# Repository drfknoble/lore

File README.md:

# Low-Cost, Open-Source Robot for Education (LORE)

## Introduction

Welcome to my repository for my Low-Cost, Open-Source Robot for Education (LORE) project.

<div>

</div>

## Motivation

I started this project because I was approached by the House of Science, a Science, Technology, Engineering, and Mathematics (STEM) organisation in Tauranga, New Zealand, who needed a low-cost, i.e., less than NZD$100.00, platform that could be used to teach robotics.

The problem was: there wasn't anything on the market at met the organisation's needs, so I decided to build one for them.

## Aims

The aims of this project included:
- Developing a low-cost, mobile robot that can be used to teach beginner, intermediate, and advanced students how to program in C++.

## Objectives

The objectives of this project included:
- Creating accessible Computer Aided Design (CAD) files.
- Creating accessible Electronics Design Automation (EDA) files.
- Creating accessible source code and software libraries.
- Creating an easy-to-assemble mobile robot that uses an Arduino microcontroller, servo motors, and ultrasonic sensors.
- Writing clear-to-follow instructions of how to program the mobile robot.

## Repository Structure

The repository is organised as follows:

```console
/lore         
    /cad                          
        /solidworks                    
        /freecad  
        /fabrication
        /renders                     
    /pcb
        /eagle
        /kicad
        /fabrication
    /src
        /beginner
        /intermediate
        /advanced
        /ROBOT
    /doc                      
        /img
        /costing                
        /programming_guide
```

All CAD files can be found in the `/cad` sub-directory. I've included the original SOLIDWORKS files and the open-source equivalents.

All EDA files can be found in the `/pcb` sub-directory. I've included the original Eagle files and the open-source equivalents.

All source code and software libaries are included in the `/src` sub-directory. The `/ROBOT` sub-directory is the Arduino library that is used to program the robot.

Documentation is included in the `/doc` sub-directory.

## Tools Used

I used the following tools in this project:
- SOLIDWORKS and FreeCAD.
- Eagle and KiCAD.
- Microsoft Visual Studio and Arduino Integrated Development IDE (IDE).

Get FreeCAD here: https://www.freecadweb.org/.  
Get KiCAD here: https://www.kicad.org/.  
Get Arduino IDE here: https://www.arduino.cc/en/software.  
Get Visual Studio here: https://visualstudio.microsoft.com/.  

Alternatively, you can use Microsoft Visual Studio Code as the IDE.

Get Code here: https://code.visualstudio.com/.

## Credit

Dr Frazer K. Noble  
http://drfknoble.com

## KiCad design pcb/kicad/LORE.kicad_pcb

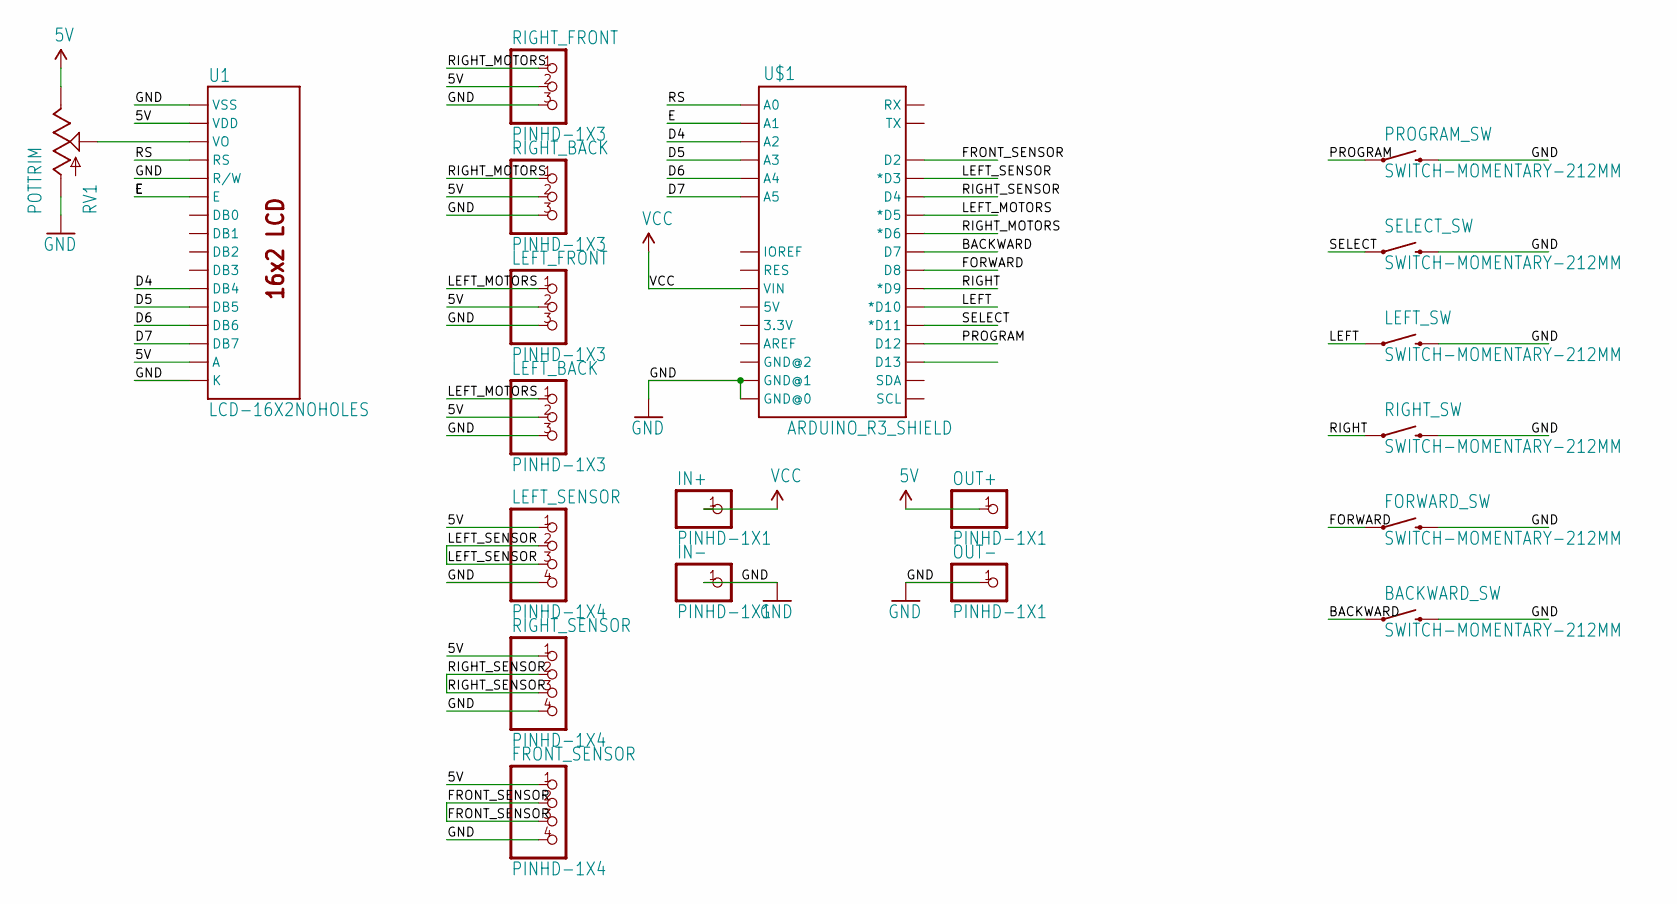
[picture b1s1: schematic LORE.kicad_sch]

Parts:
BACKWARD_SW: SWITCH-MOMENTARY-212MM; TACTILE-PTH-12MM
FORWARD_SW: SWITCH-MOMENTARY-212MM; TACTILE-PTH-12MM
FRONT_SENSOR: PINHD-1X4; 1X04
IN+: PINHD-1X1; 1X01
IN-: PINHD-1X1; 1X01
LEFT_BACK: PINHD-1X3; 1X03
LEFT_FRONT: PINHD-1X3; 1X03
LEFT_SENSOR: PINHD-1X4; 1X04
LEFT_SW: SWITCH-MOMENTARY-212MM; TACTILE-PTH-12MM
OUT+: PINHD-1X1; 1X01
OUT-: PINHD-1X1; 1X01
PROGRAM_SW: SWITCH-MOMENTARY-212MM; TACTILE-PTH-12MM
RIGHT_BACK: PINHD-1X3; 1X03
RIGHT_FRONT: PINHD-1X3; 1X03
RIGHT_SENSOR: PINHD-1X4; 1X04
RIGHT_SW: SWITCH-MOMENTARY-212MM; TACTILE-PTH-12MM
RV1: POTTRIM; TRIM_POT
SELECT_SW: SWITCH-MOMENTARY-212MM; TACTILE-PTH-12MM
U1: LCD-16X2NOHOLES; LCD-16X2_NOHOLES
U$1: ARDUINO_R3_SHIELD; UNO_R3_SHIELD

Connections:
5V: FRONT_SENSOR.1, LEFT_BACK.2, LEFT_FRONT.2, LEFT_SENSOR.1, OUT+.1, RIGHT_BACK.2, RIGHT_FRONT.2, RIGHT_SENSOR.1, RV1.2 (E), U1.2 (VDD), U1.15 (A)
BACKWARD: BACKWARD_SW.1, U$1.D7
D4: U1.11 (DB4), U$1.A2
D5: U1.12 (DB5), U$1.A3
D6: U1.13 (DB6), U$1.A4
D7: U1.14 (DB7), U$1.A5
E: U1.6 (E), U$1.A1
FORWARD: FORWARD_SW.1, U$1.D8
FRONT_SENSOR: FRONT_SENSOR.2, FRONT_SENSOR.3, U$1.D2
GND: BACKWARD_SW.3 (2), FORWARD_SW.3 (2), FRONT_SENSOR.4, IN-.1, LEFT_BACK.3, LEFT_FRONT.3, LEFT_SENSOR.4, LEFT_SW.3 (2), OUT-.1, PROGRAM_SW.3 (2), RIGHT_BACK.3, RIGHT_FRONT.3, RIGHT_SENSOR.4, RIGHT_SW.3 (2), RV1.3 (A), SELECT_SW.3 (2), U1.1 (VSS), U1.5 (R/W), U1.16 (K), U$1.GND@0, U$1.GND@1
LEFT: LEFT_SW.1, U$1.D10 (*D10)
LEFT_MOTORS: LEFT_BACK.1, LEFT_FRONT.1, U$1.D5 (*D5)
LEFT_SENSOR: LEFT_SENSOR.2, LEFT_SENSOR.3, U$1.D3 (*D3)
unnamed: RV1.1 (S), U1.3 (VO)
PROGRAM: PROGRAM_SW.1, U$1.D12
RIGHT: RIGHT_SW.1, U$1.D9 (*D9)
RIGHT_MOTORS: RIGHT_BACK.1, RIGHT_FRONT.1, U$1.D6 (*D6)
RIGHT_SENSOR: RIGHT_SENSOR.2, RIGHT_SENSOR.3, U$1.D4
RS: U1.4 (RS), U$1.A0
SELECT: SELECT_SW.1, U$1.D11 (*D11)
VCC: IN+.1, U$1.VIN

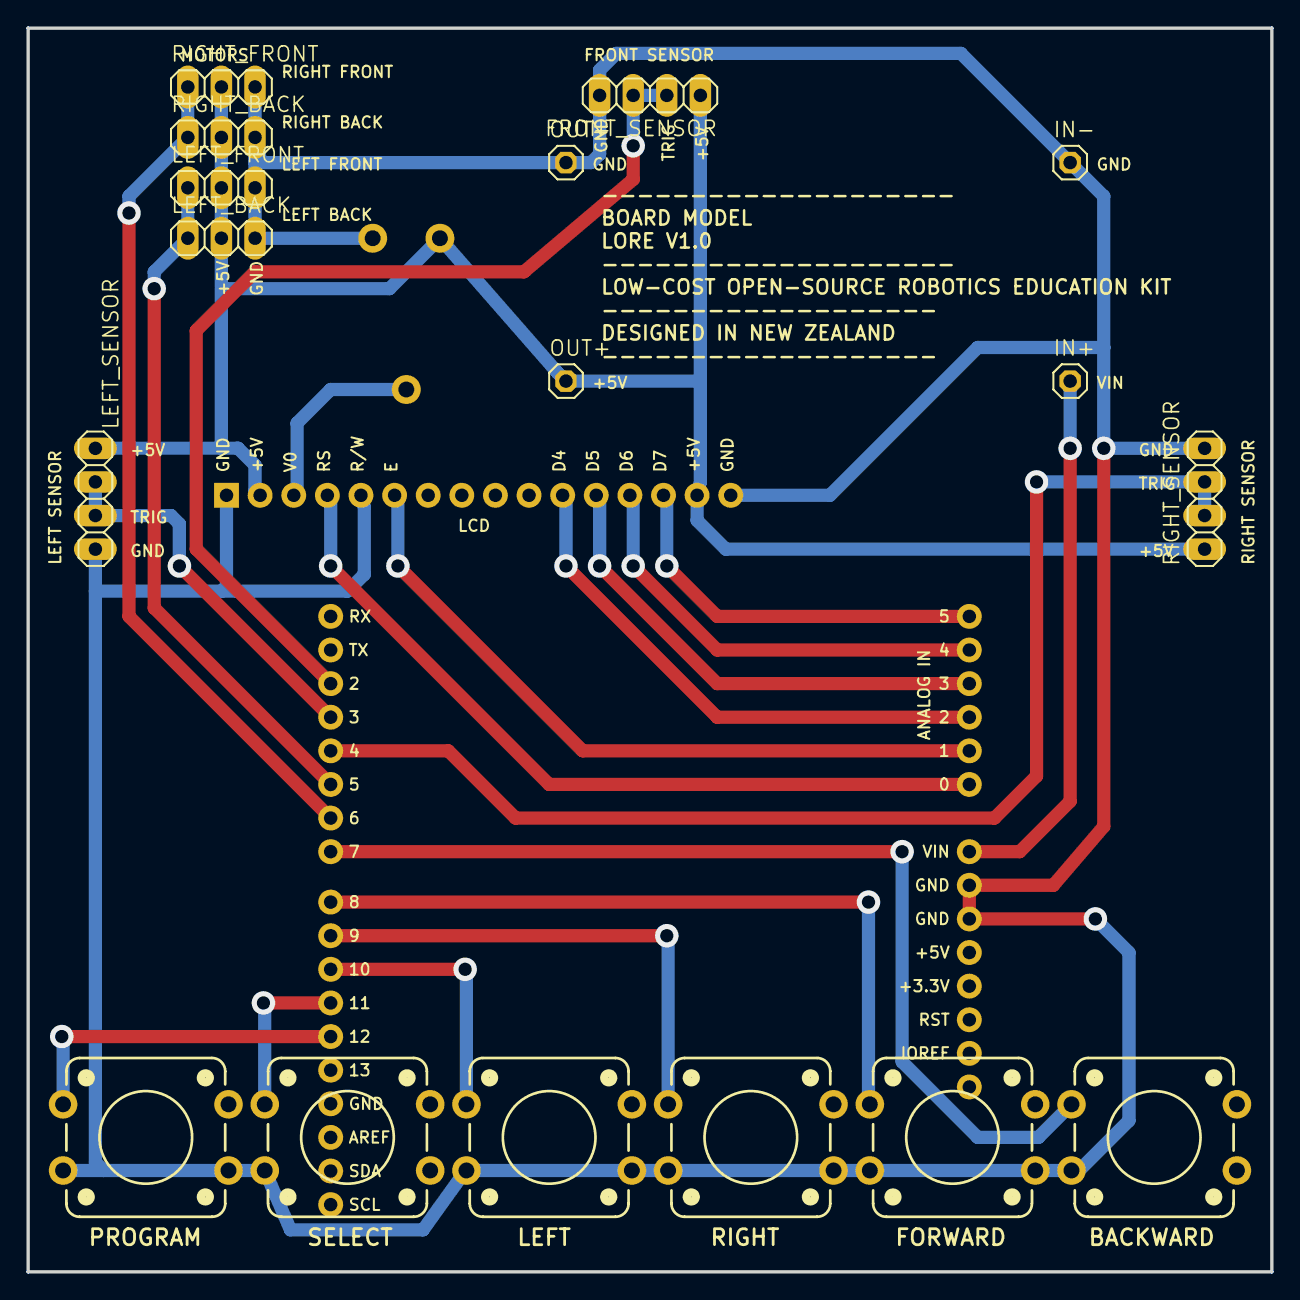
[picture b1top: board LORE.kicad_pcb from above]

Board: 2 copper layers, 94.0 x 94.0 mm, 20 parts (0 on the bottom side), 21 nets.

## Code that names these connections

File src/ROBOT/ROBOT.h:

/*
*	ROBOT.h - Libary for controlling the Low-Cost Open-Source Robotic Education (LORE) kit.
*	Version 1.1.
*	Copyright (c) 2014 Dr. Frazer K. Noble. All rights reserved.
*
*	Low-cost Open-source Robotics Educational (LORE) kits are provided "as is" with no warranties whatsoever,
* 	including any warranty of merchantability, non - infringement, fitness for any particular purpose,
* 	or any warranty otherwise arising out of any proposal, specification or sample.
* 	LORE kits (and manufacturers and distributors) disclaim all liability, including liability for infringement of any proprietary rights,
*	relating to use of information in any documents and files and software and no license, express or implied, by LORE kits or otherwise,
*	to any intellectual property rights is granted herein. LORE kits(and manufacturers and distributors) assumes no responsibility or liability
*	for any errors or inaccuracies that may appear in any documentation or files or any software that may be provided.
*	The information in any documents or files is furnished for informational use only, is subject to change without notice,
*	and should not be construed as a commitment by LORE kits(and manufacturers and distributors).
*/

/*
*	The LORE robot is controlled by the following functions.
*
*	The functions are:
*
*	initialise()				- Initialises the LORE robot's pins' states (LOW/HIGH) and direction (INPUT/OUTPUT).
*	move(int direction)			- Moves the robot in the desired direction (LEFT, RIGHT, FORWARD, BACKWARD).
*	readSensor(int sensor)		- Takes a measurement from a sensor (FRONT_SENSOR, LEFT_SENSOR, RIGHT_SENSOR)
*								  and returns the distanc measured.
*	buttonPressed(int button)	- Checks to see if the a button (PROGRAM, SELECT, LEFT, RIGHT, FORWARD, BACKWARD)
*								  is pressed.
*	writeLCD(char* string)		- Writes a series of characters to the LORE robot's LCD panel.
*
*/

#ifndef ROBOT_h
#define ROBOT_h

/*
 *	Defines for the LORE robot used with the ROBOT library.
 */

//	Button #defines

#define BACKWARD 7
#define FORWARD 8
#define RIGHT 9
#define LEFT 10
#define SELECT 11
#define PROGRAM 12

// LCD #defines

#define RS A0
#define E A1
#define D4 A2
#define D5 A3
#define D6 A4
#define D7 A5

//	Sensor #defines

#define FRONT_SENSOR 2
#define LEFT_SENSOR 3
#define RIGHT_SENSOR 4

//	Motor #defines

#define LEFT_MOTORS 5
#define RIGHT_MOTORS 6

//	Functions 


class ROBOT {

public:

	ROBOT();

	bool initialise();

	bool buttonPressed(int button);
	bool clear();
	bool move(int direction);
	bool turn(int direction);
	bool program(int direction);
	bool run();
	bool writeLCD(char* string);
	long measureDistance(int sensor);
	bool setTurnTime(int direction, int time);

private:

	int leftTurnTime;
	int rightTurnTime;

	long programDebounceTime;
	bool programState;
	bool programPrevState;

	long selectDebounceTime;
	bool selectState;
	bool selectPrevState;

	long leftDebounceTime;
	bool leftState;
	bool leftPrevState;

	long rightDebounceTime;
	bool rightState;
	bool rightPrevState;

	long forwardDebounceTime;
	bool forwardState;
	bool forwardPrevState;

	long backwardDebounceTime;
	bool backwardState;
	bool backwardPrevState;

	long frontSensorValue;
	long leftSensorValue;
	long rightSensorValue;

	long debounceDelay;

	char programString[50];
	int programSet;
	int programSize;

	bool readButton(int button, bool &buttonState, bool &buttonPrevState, long &debounceTime);
	bool readSensor(int sensor, long &distance);

};

#endif

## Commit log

2022-11-02 Minor tweak.
2022-11-02 Minor tweaks.
2022-11-02 Updated CAD models and exported open-source equivalents.
2022-11-03 Added renders to file.
2022-11-07 Added some photos of the actual robot.
2022-11-08 Fixed reference to library in README.md
